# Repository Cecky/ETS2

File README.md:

# Project
TelemetryClient and ButtonBox for Euro Truck Simulator 2 and American Truck 
Simulator

# Why?
Just a simple and dirty project to increase the fun while playing ETS2 and ATS ;-)

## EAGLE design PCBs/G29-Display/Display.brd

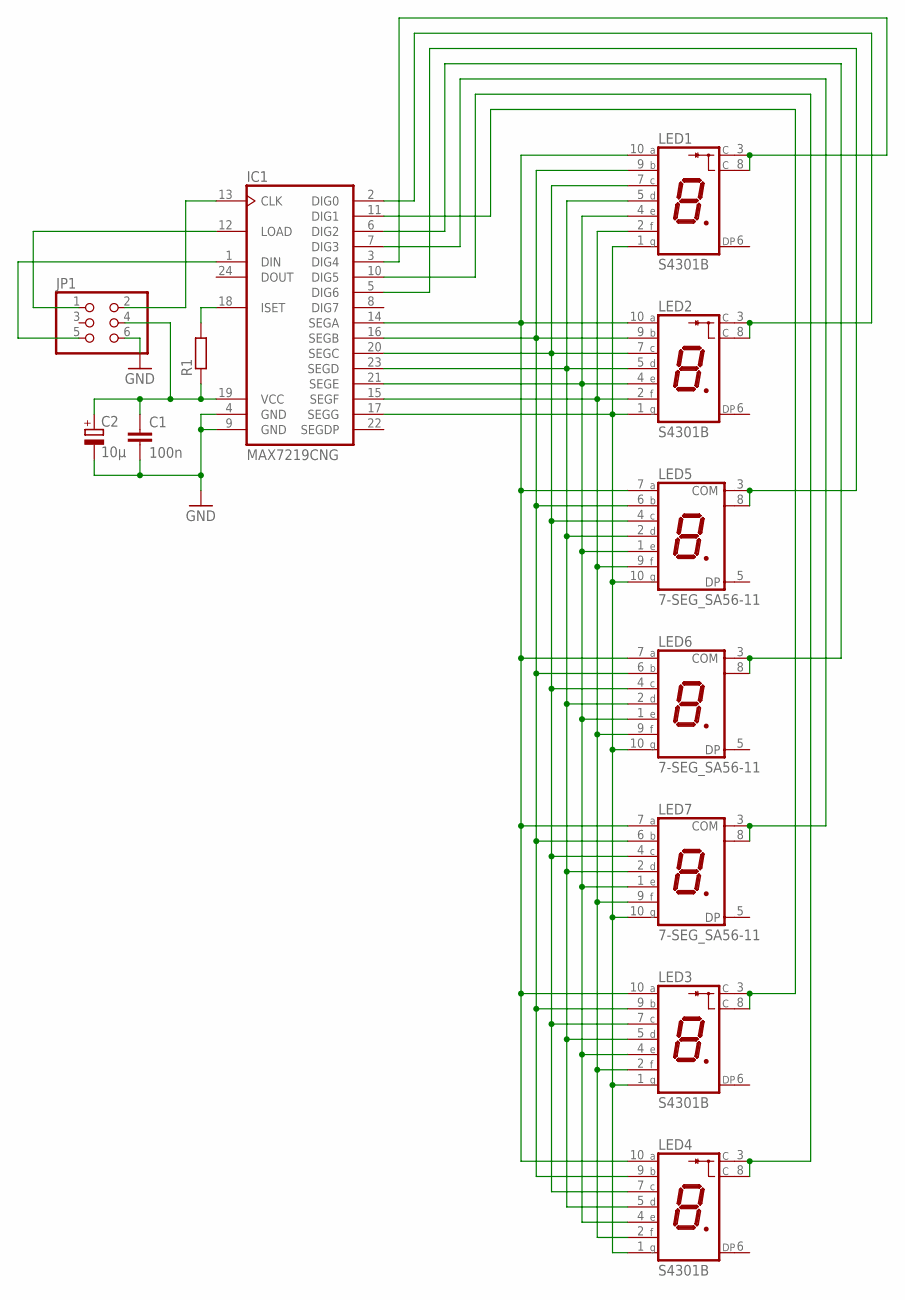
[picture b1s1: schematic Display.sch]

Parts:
C1: 100n; C0805
C2: 10µ; PANASONIC_B
IC1: MAX7219CNG; DIL24-3
JP1: PINHD-2X03_2.54; 2X03
LED1, LED2, LED3, LED4: S4301B
LED5, LED6, LED7: 7-SEG_SA56-11; SA56-11
R1: R-EU_R0805; R0805

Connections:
GND: C1.2, C2.-, IC1.4 (GND), IC1.9 (GND), JP1.6
unnamed: IC1.17 (SEGG), LED1.1 (G), LED2.1 (G), LED3.1 (G), LED4.1 (G), LED5.10 (G), LED6.10 (G), LED7.10 (G)
unnamed: IC1.15 (SEGF), LED1.2 (F), LED2.2 (F), LED3.2 (F), LED4.2 (F), LED5.9 (F), LED6.9 (F), LED7.9 (F)
unnamed: IC1.21 (SEGE), LED1.4 (E), LED2.4 (E), LED3.4 (E), LED4.4 (E), LED5.1 (E), LED6.1 (E), LED7.1 (E)
unnamed: IC1.23 (SEGD), LED1.5 (D), LED2.5 (D), LED3.5 (D), LED4.5 (D), LED5.2 (D), LED6.2 (D), LED7.2 (D)
unnamed: IC1.20 (SEGC), LED1.7 (C), LED2.7 (C), LED3.7 (C), LED4.7 (C), LED5.4 (C), LED6.4 (C), LED7.4 (C)
unnamed: IC1.16 (SEGB), LED1.9 (B), LED2.9 (B), LED3.9 (B), LED4.9 (B), LED5.6 (B), LED6.6 (B), LED7.6 (B)
unnamed: IC1.14 (SEGA), LED1.10 (A), LED2.10 (A), LED3.10 (A), LED4.10 (A), LED5.7 (A), LED6.7 (A), LED7.7 (A)
unnamed: IC1.3 (DIG4), LED1.3 (C), LED1.8 (C)
unnamed: IC1.2 (DIG0), LED2.3 (C), LED2.8 (C)
unnamed: IC1.5 (DIG6), LED5.3 (COM), LED5.8 (COM)
unnamed: IC1.6 (DIG2), LED6.3 (COM), LED6.8 (COM)
unnamed: IC1.7 (DIG3), LED7.3 (COM), LED7.8 (COM)
unnamed: IC1.10 (DIG5), LED4.3 (C), LED4.8 (C)
unnamed: IC1.11 (DIG1), LED3.3 (C), LED3.8 (C)
unnamed: IC1.1 (DIN), JP1.5
unnamed: IC1.12 (LOAD), JP1.1
unnamed: IC1.13 (CLK), JP1.2
unnamed: C1.1, C2.+, IC1.19 (VCC), JP1.4, R1.1
unnamed: IC1.18 (ISET), R1.2

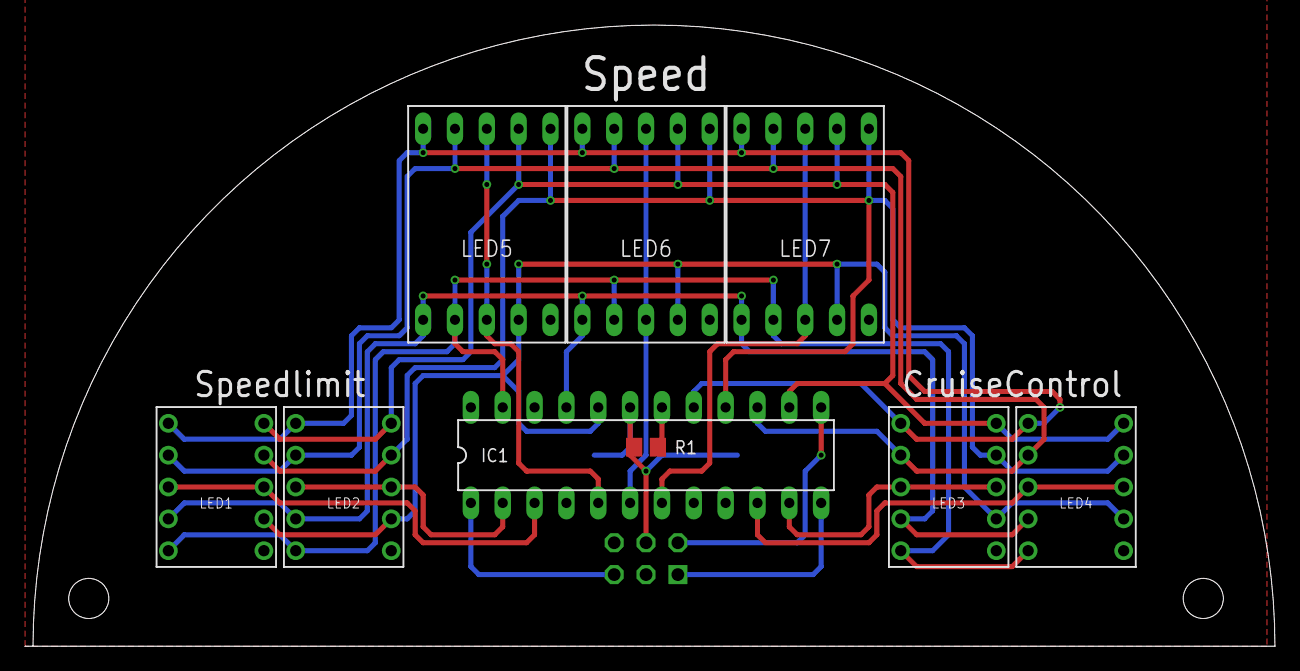
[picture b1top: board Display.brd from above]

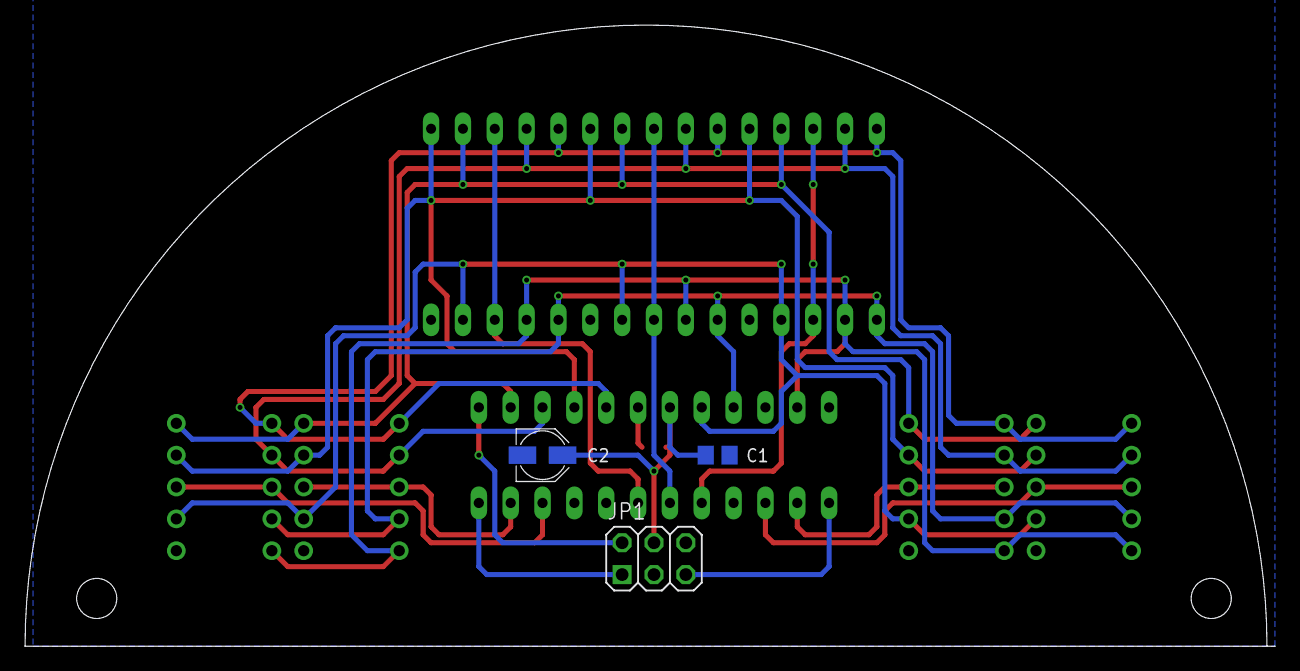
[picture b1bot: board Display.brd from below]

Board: 2 copper layers, 99.7 x 49.6 mm, 12 parts (3 on the bottom side), 20 nets.

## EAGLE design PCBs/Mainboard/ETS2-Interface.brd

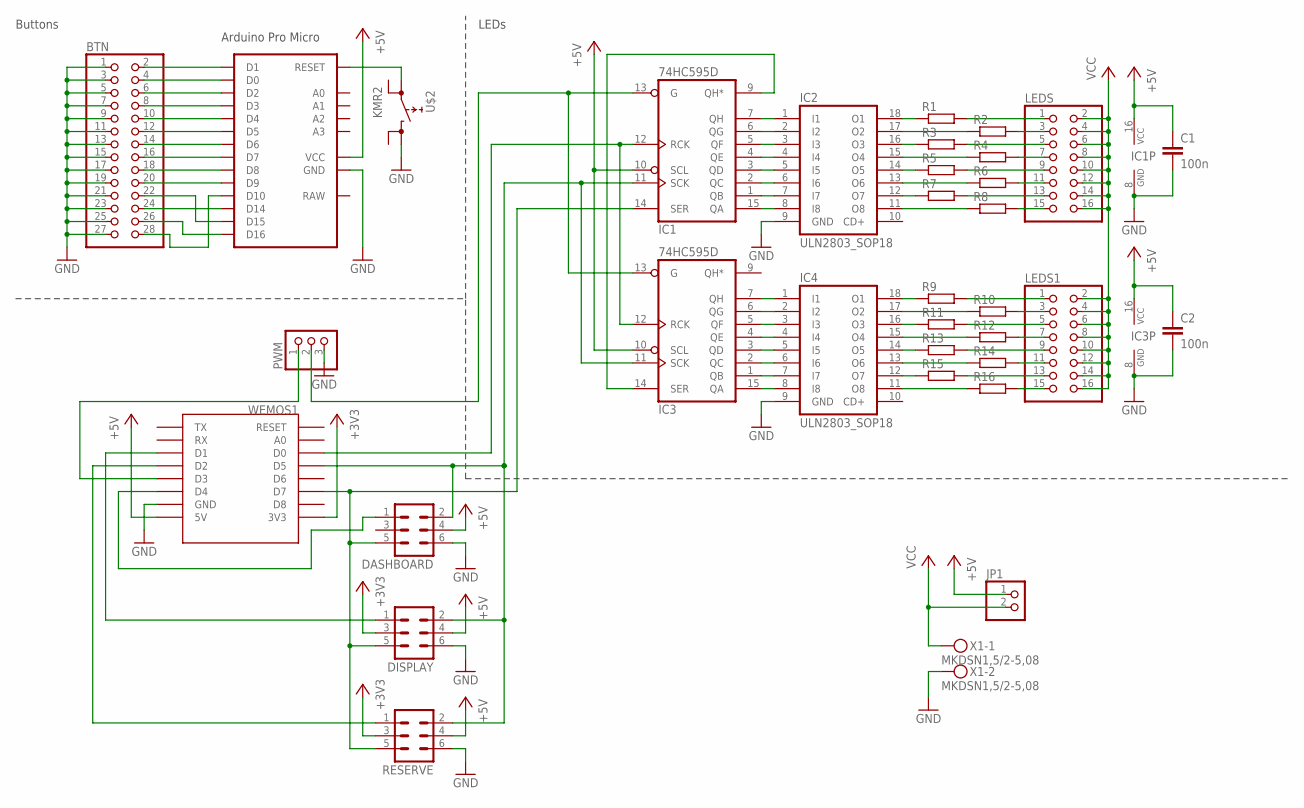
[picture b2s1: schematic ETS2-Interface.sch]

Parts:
BTN: PINHD-2X14_2.54; 2X14
C1, C2: 100n; C0805
DASHBOARD: ML6
DISPLAY: ML6
IC1, IC3: 74HC595D; SO16
IC2, IC4: ULN2803_SOP18; SOP18
JP1: PINHD-1X02_2.54-S; 1X02-S
LEDS, LEDS1: PINHD-2X08_2.54; 2X08
PWM: PINHD-1X03_2.54-S; 1X03-S
R1, R2, R3, R4, R5, R6, R7, R8, R9, R10, R11, R12, R13, R14, R15, R16: R-EU_R0805; R0805
RESERVE: ML6
U$1: PRO-MICRO
U$2: KMR2
WEMOS1: WEMOS-D1-MINI
X1: MKDSN1,5/2-5,08

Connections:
+3V3: DISPLAY.3, RESERVE.3, WEMOS1.3V3
+5V: C1.1, C2.1, DASHBOARD.4, DISPLAY.4, IC1.10 (SCL), IC1.16 (VCC), IC3.10 (SCL), IC3.16 (VCC), JP1.1, RESERVE.4, U$1.VCC, WEMOS1.5V
CLOCK: DASHBOARD.2, DISPLAY.2, IC1.11 (SCK), IC3.11 (SCK), RESERVE.2, WEMOS1.D5
GND: BTN.1, BTN.3, BTN.5, BTN.7, BTN.9, BTN.11, BTN.13, BTN.15, BTN.17, BTN.19, BTN.21, BTN.23, BTN.25, BTN.27, C1.2, C2.2, DASHBOARD.6, DISPLAY.6, IC1.8 (GND), IC2.9 (GND), IC3.8 (GND), IC4.9 (GND), PWM.3, RESERVE.6, U$1.GND, U$1.GND1 (GND), U$1.GND2 (GND), U$2.3 (1), WEMOS1.GND, X1.2
LATCH: DASHBOARD.1, WEMOS1.D4
MOSI: DASHBOARD.5, DISPLAY.5, IC1.14 (SER), RESERVE.5, WEMOS1.D7
unnamed: BTN.2, U$1.D1
unnamed: BTN.4, U$1.D0
unnamed: BTN.6, U$1.D2
unnamed: BTN.8, U$1.D3
unnamed: BTN.10, U$1.D4
unnamed: BTN.12, U$1.D5
unnamed: BTN.14, U$1.D6
unnamed: BTN.16, U$1.D7
unnamed: BTN.18, U$1.D8
unnamed: BTN.20, U$1.D9
unnamed: IC1.7 (QH), IC2.1 (I1)
unnamed: IC1.6 (QG), IC2.2 (I2)
unnamed: IC1.5 (QF), IC2.3 (I3)
unnamed: IC1.4 (QE), IC2.4 (I4)
unnamed: IC1.3 (QD), IC2.5 (I5)
unnamed: IC1.2 (QC), IC2.6 (I6)
unnamed: IC1.1 (QB), IC2.7 (I7)
unnamed: IC1.15 (QA), IC2.8 (I8)
unnamed: IC2.18 (O1), R1.1
unnamed: IC2.17 (O2), R2.1
unnamed: IC2.16 (O3), R3.1
unnamed: IC2.15 (O4), R4.1
unnamed: IC2.14 (O5), R5.1
unnamed: IC2.13 (O6), R6.1
unnamed: IC2.12 (O7), R7.1
unnamed: IC2.11 (O8), R8.1
unnamed: LEDS.15, R8.2
unnamed: LEDS.13, R7.2
unnamed: LEDS.11, R6.2
unnamed: LEDS.9, R5.2
unnamed: LEDS.7, R4.2
unnamed: LEDS.5, R3.2
unnamed: LEDS.3, R2.2
unnamed: LEDS.1, R1.2
unnamed: BTN.28, U$1.D10
unnamed: BTN.26, U$1.D16
unnamed: BTN.24, U$1.D14
unnamed: BTN.22, U$1.D15
unnamed: IC3.7 (QH), IC4.1 (I1)
unnamed: IC3.6 (QG), IC4.2 (I2)
unnamed: IC3.5 (QF), IC4.3 (I3)
unnamed: IC3.4 (QE), IC4.4 (I4)
unnamed: IC3.3 (QD), IC4.5 (I5)
unnamed: IC3.2 (QC), IC4.6 (I6)
unnamed: IC3.1 (QB), IC4.7 (I7)
unnamed: IC3.15 (QA), IC4.8 (I8)
unnamed: IC4.18 (O1), R9.1
unnamed: IC4.17 (O2), R10.1
unnamed: IC4.16 (O3), R11.1
unnamed: IC4.15 (O4), R12.1
unnamed: IC4.14 (O5), R13.1
unnamed: IC4.13 (O6), R14.1
unnamed: IC4.12 (O7), R15.1
unnamed: IC4.11 (O8), R16.1
unnamed: LEDS1.15, R16.2
unnamed: LEDS1.13, R15.2
unnamed: LEDS1.11, R14.2
unnamed: LEDS1.9, R13.2
unnamed: LEDS1.7, R12.2
unnamed: LEDS1.5, R11.2
unnamed: LEDS1.3, R10.2
unnamed: LEDS1.1, R9.2
unnamed: RESERVE.1, WEMOS1.D2
unnamed: IC1.9 (QH*), IC3.14 (SER)
unnamed: IC1.12 (RCK), IC3.12 (RCK), WEMOS1.D0
unnamed: DISPLAY.1, WEMOS1.D1
unnamed: PWM.1, WEMOS1.D3
unnamed: IC1.13 (G), IC3.13 (G), PWM.2
unnamed: U$1.RESET, U$2.1 (0)
VCC: JP1.2, LEDS.2, LEDS.4, LEDS.6, LEDS.8, LEDS.10, LEDS.12, LEDS.14, LEDS.16, LEDS1.2, LEDS1.4, LEDS1.6, LEDS1.8, LEDS1.10, LEDS1.12, LEDS1.14, LEDS1.16, X1.1

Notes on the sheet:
Buttons
Arduino Pro Micro
LEDs

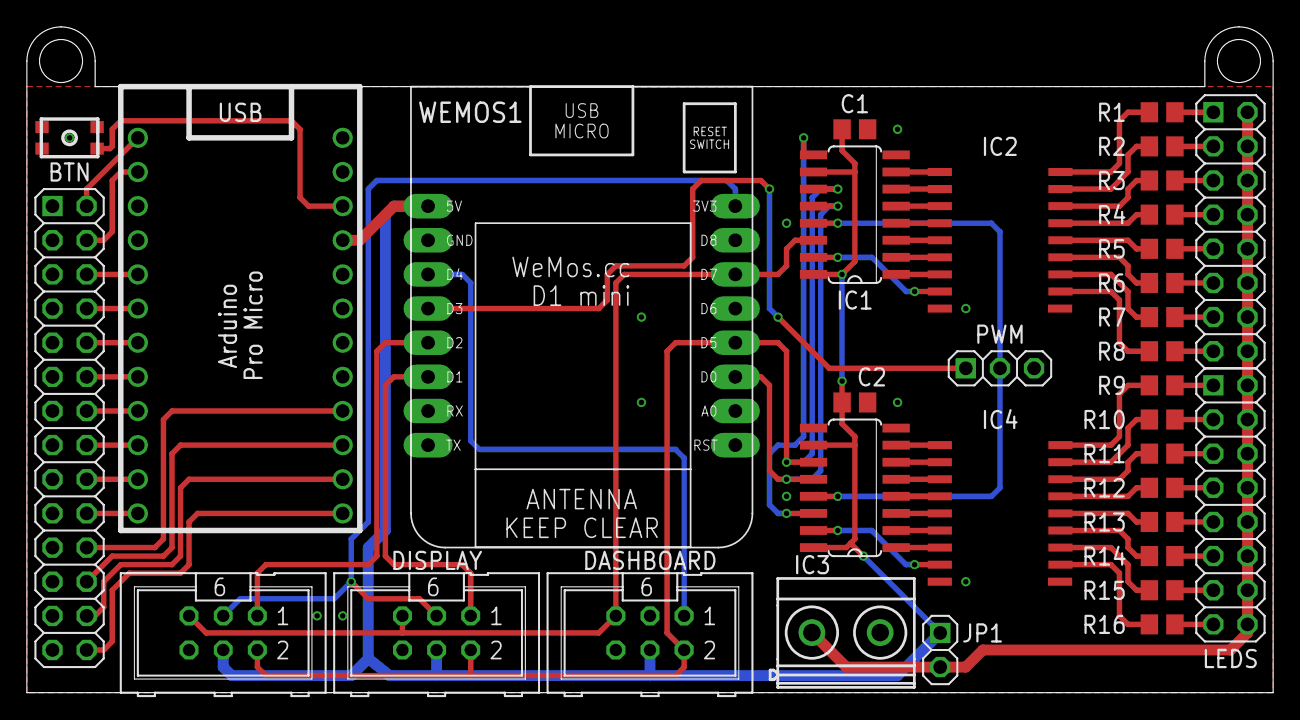
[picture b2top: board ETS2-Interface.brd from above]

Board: 2 copper layers, 92.7 x 49.5 mm, 34 parts (0 on the bottom side), 76 nets.

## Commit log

2019-06-06 added some leds
2019-06-06 changed buttons for engine start
2019-06-08 update leds only if ledstate changed
2020-03-28 + added gametimedependant pwm for leds
    optimizations to some function calls due to stackissues because of the many copies of the payloadstring
2024-02-19 Add files via upload
    - moved led and max7219 update to cyclic interrupt
2024-04-07 - adaptation to new dataformat
2024-12-07 Add files via upload
    - rework of datahandling
    - add "ElectricOn"
